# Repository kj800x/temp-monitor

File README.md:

# temp-monitor

# Contributors

kj800x

# Anti-contributors

bent0b0x

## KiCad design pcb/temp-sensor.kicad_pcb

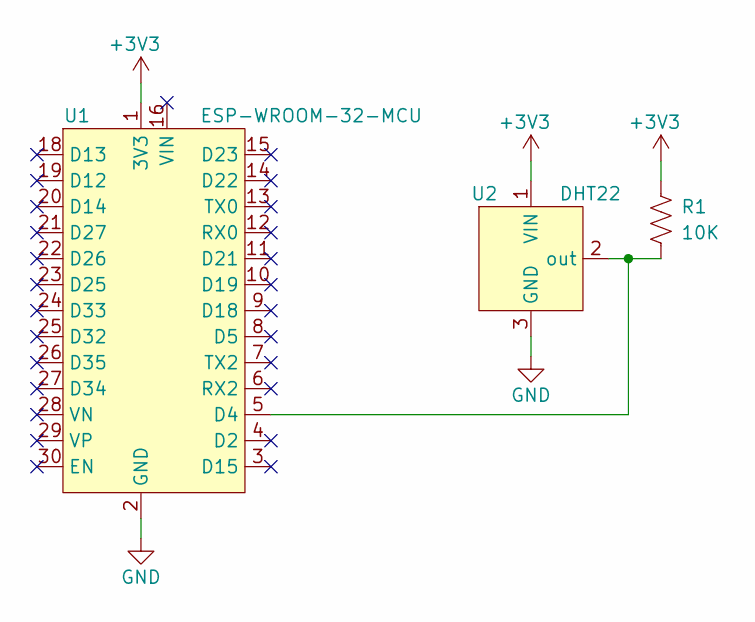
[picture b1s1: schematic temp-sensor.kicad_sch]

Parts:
R1: 10K; R_Axial_DIN0614_L14.3mm_D5.7mm_P15.24mm_Horizontal
U1: ESP-WROOM-32-MCU
U2: DHT22; TerminalBlock_TE_282834-3_1x03_P2.54mm_Horizontal

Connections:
+3V3: R1.1, U1.1 (3V3), U2.1 (VIN)
GND: U1.2 (GND), U1.17 (GND), U2.3 (GND)
unnamed: R1.2, U1.5 (D4), U2.2 (out)

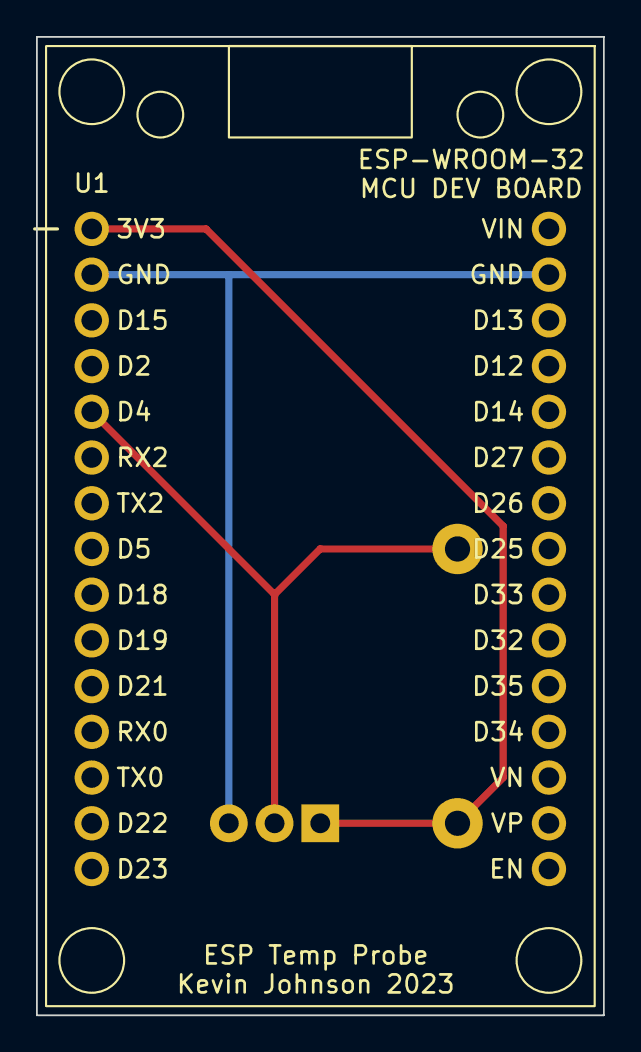
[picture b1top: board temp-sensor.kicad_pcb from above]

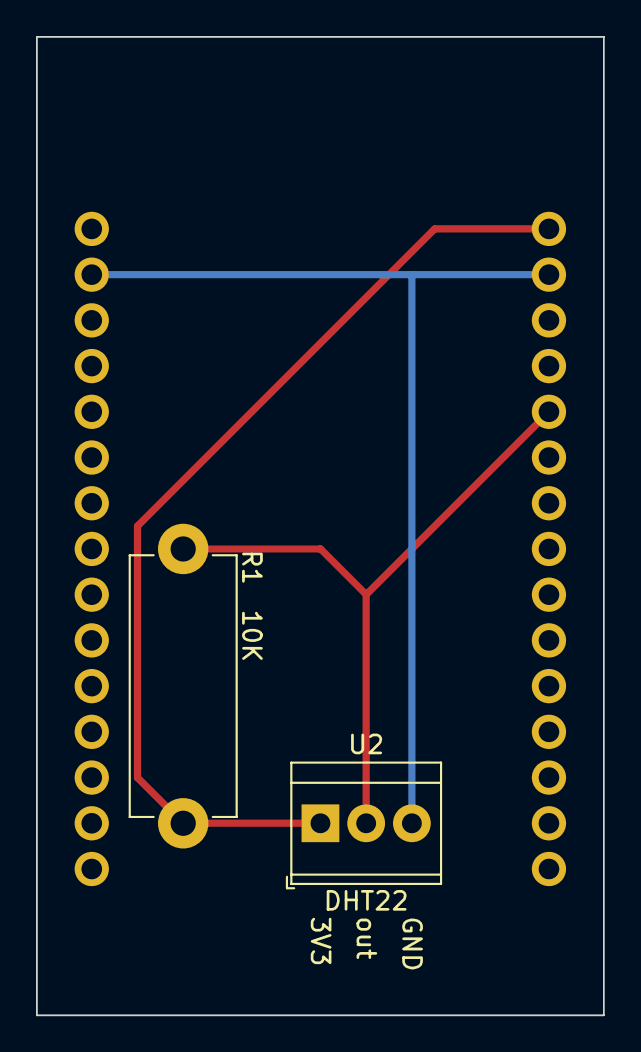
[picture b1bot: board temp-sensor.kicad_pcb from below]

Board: 2 copper layers, 31.5 x 54.4 mm, 3 parts (2 on the bottom side), 3 nets.

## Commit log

2020-03-24 initial
2020-03-27 Board mostly done
2020-03-27 Finish Layout add gerbers
2020-07-27 Adjust for new components
2020-08-01 Add BOM
2020-08-10 logic readings
2020-08-10 Complete board-fixed
2020-08-18 Pcb changes
2020-08-19 Remake Board based on v2 fixes
2020-08-19 Check in V2 Gerbers
2020-10-17 Schematic upgrads
2020-10-30 move files
2020-10-30 ui folder
2020-10-30 server folder
2020-10-31 Better derivation for motor and status
2020-10-31 pressure deploy check
2020-10-31 Better pressure sending, logging, state derivation
2020-11-01 pressure cleanup
2020-11-01 support real pressure
2020-11-01 Limit ranges
2020-11-01 pressure has different range
2020-11-01 Remove logging
2020-11-01 Send floats instead of strings
2020-11-01 Check in lost files
2020-11-04 Support time offset for csv pressure
2020-11-04 improved status estimation
2020-11-04 Make real pressure disconnect tolerant
2020-11-04 add bonescript dep
2020-11-04 Schematic update
2020-11-04 Motor output
2020-11-04 live tweeks
2020-11-15 Motor fixes
2020-11-16 Prep for replay mode
2020-11-17 GraphQL support
2020-11-18 Completed pretty much all of the features for replay mode
2020-11-22 csv in browser
2020-11-22 dataSpec
2020-11-23 Programming support
2020-11-28 New proposal
2020-11-28 gsch2pcb
2020-11-28 BBGW footprint and regenerate PCB
2020-11-29 Motor controller wip
2020-11-29 Finished board pending tweaks
2020-11-29 Order 3 finalized
2021-01-25 Upgrade @kj800x/localproxy-client to 0.3.0
2021-01-25 Upgrade @kj800x/localproxy-react-scripts to 0.3.0
2021-01-25 fixes for localproxy@0.3.0
2021-02-21 Upgrade schematic
2021-02-21 Board updates
2021-02-22 Use updated program for netlist
2021-02-22 Update schematic finalize board
2021-02-22 Update net
2021-02-22 Finalize for larger box
2021-08-11 Repurpose for the temperature monitor
2021-08-11 Chartas just a little bit bigger
2021-08-11 Responsive
2021-08-12 Bucket the data so we aren't storing every single data point
2021-08-12 Clean up chart panel formatting
2021-08-13 Increase perfomance a bit
2021-08-13 Probe changes
2021-08-16 O(n) is better than O(nn)
2021-08-16 Oops
2021-08-16 BE support for replay data
2021-08-16 RM logs
2021-08-17 Lotsa improvements
2021-08-17 off by hour fix
2021-11-21 Upgrade @kj800x/localproxy-client to 0.3.3
2021-11-21 Upgrade @kj800x/localproxy-react-scripts to 0.3.3
2021-12-13 rewrite
2021-12-13 Rewrite probe
2021-12-13 Proper typing for Date
2021-12-13 Send temperature probe to ec2
2021-12-13 Use subscriptions endpoint which supports deployed queries
2021-12-14 Slight adjustments to the recharts config
2021-12-15 Some more chart improvements
2022-01-10 Add legend and support hiding series
2022-01-10 Support historical queries and viewing historical dates in the ui
2022-01-13 Add ec2-deploy section to make deployment scriptable
2022-01-19 Fix the data processing so that stuff isn't jumping everywhere
2022-02-02 Update localproxy versions
2022-02-02 Update server to require humidity measurements as well
2022-02-02 Update probe to use DHT22 on pin 22
2022-02-02 Remove log line
2022-02-04 Fix #5
2022-02-04 PR feedback
2022-02-04 yeet try this
2022-02-04 This?
    https://stackoverflow.com/questions/68527897/how-to-specifiy-path-for-actions-setup-node-in-github
2022-02-04 whoops again
2022-02-06 Require API key
2022-02-06 Use JWT tokens rather than flat text files
2022-02-06 Switch probe to JWT
2022-02-06 self-nits
2022-02-06 Easter egg
2022-02-06 req is undefined for subscriptions
2022-02-07 Display humidity
2022-02-07 Mucking around with the chart
2022-02-07 Don't crash the app if there's no data
2022-02-07 Support 7 day chart. resolves #3
2022-02-07 Lint
2022-02-07 Support high low
2022-02-07 Fixes
2022-07-27 Make authRequired function
2022-11-20 Upgrade to Node 18.12.1
2022-12-30 Basic Rust probe
2022-12-31 Actually connect to the wifi
2022-12-31 Actually record data
2022-12-31 Add PCB for ESP probe
2023-01-01 Finish rust probe
2023-01-02 Use dht-embedded=0.2.0 (https://github.com/kelnos/dht-embedded-rs/pull/1)
2023-02-11 WIP not working
